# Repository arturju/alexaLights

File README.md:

# alexaLights
----
My original intent was to integrate a Particle Photon board with an Amazon Echo device to control some devices using voice commands. In the process, I found projects by people who had done similar things (see references) and used those as guides. This is my attemt at bringing together a few of the things I learned on the way.

First, the user issues a voice command to the Amazon Echo device. The device sends the audio to Amazon's Alexa Voice service which 'tokenizes' the speech into a json format. It then gets routed to the specified endpoint (our AWS Lambda Function) and passes the tokenized values into the function call to Particle's API. This triggers our Particle Photon device to change state and return an *int* to the Lambda Function. The Lambda Function finishes the request and sends a voice response back for the Amazon Echo device along with an optional reference card for the companion app.

----
## Hardware and Particle

Let's start at the last step of the process; the Particle Photon. I wanted to control an LED strip which needed a voltage higher than what the Particle Photon could provide so I got a [power supply](https://www.amazon.com/gp/product/B005T7NIAI/ref=oh_aui_detailpage_o06_s00?ie=UTF8&psc=1) that could provide 24V for the LED strip and 5V for for the board. To switch this load I used a [TIP120](https://www.adafruit.com/product/976) Darlington transistor and wired it to the board according to the schematics. Finally, a [PIR sensor](https://www.adafruit.com/product/189) allows the controller to automatically turn the lights on/off if certain timers have elapsed.

The main loop in the Photon runs a state machine that reads any inputs, updates the status of pins, checks flags and timers, and remembers the last state of the input pin. The following lines of code connect the locally defined functions, *turnPinOnOff* and *partyFunc*, to Particle's cloud. This will allow us to call these functions from other code.
```C
    Spark.function("myFunction", turnPinOnOff);
    Spark.function("globalParty", partyFunc);
```
Calling the function will trigger a change in one of the flags or pin values and this gets picked up the next time the main loops runs through.

----
## Lambda Function

I won't go into detail on how to create an AWS account (you can see the tutorials on the references for more details) but I'll touch on some points that I think are important. The relevant files for the Lambda Function are in the *customSkill/src/* directory (more about Smart Home Skills in a bit). You will need to edit the *sampleConfig.js* file with your Particle board's information, your deviceID and acccesToken, and rename it to *config.js*. 
The main code is in *index.js* file but before we take a look at it we must understand the structure of an Alexa Custom Skill command. A command consists of a **wake word**, Alexa, an **invocation name** and an **intent** with optional **slots**.

The Lambda Function receives the aforementioned parameters in a JSON format (more on this later), switches to the appropiate case based on the **intent**, uses the **slots** to construct a message, and sends it off to the Particle board. Many Intents can be assigned to the Custom Skill giving it much more versatility than a Smart Home Skill. 

We can also design a response card to the companion Alexa App that can display extra information for the user. The fastest way to get up and running is to select *AlexaSkill.js, config.js, index.js* zip them, and upload directly to the Lambda Function page.

For the user, the main difference between a Custom Skill and a Smart Home Skill is the way in which it's called. A Smart Home Skill does not need an invocation name, so our command would be _'Alexa, turn the Kitchen Lights On'_. This is much easier to remember but unfortunately the backend limits the responses back to the users and requires an OAuth to authenticate with your device making things a bit more complicated. I was not able to succesfully authenticate with my Particle device but I put the code up anyways in case anyone wants to try it. That's in the _smartHomeSkill/_ directory.

----
## Alexa Skills Kit (ASK)

This part of the code is responsible for defining your **invocation name**, **intents**, and **slots** (code can be found in *customSkill/speechAssets/*). The Interaction Model of the Custom Skill contains Sample Utterances that are used to correctly identify your request. For example, the *onOffIntent* is defined by the phrase ('Alexa, *tell/ask* *The House*' is assummed) 'to turn the _Kitchen Lights_ _Off_'. 
```
onOffIntent to turn the {deviceName} {onOrOff}
```
The Intent Schema connects your Sample Utterances to the JSON format in which it will get passed to the Lambda Function. For the onOffIntent we have the following Intent Schema:

``` javascript
{
 "intents": [
   {
    "intent": "onOffIntent",
     "slots": [
       {
        "name": "onOrOff",
        "type": "ON_OFF"
       },
       {
        "name": "deviceName",
        "type": "DEVICE_NAMES"
       }
      ] 
   }
  ]
}
```
The last important part of the Alexa Skill Kit are the Custom Slot Types which are like macros. For example:
```
DEVICE_NAMES
kitchen lights
living room lights
```

----
## Result

Picture and video:

----

## References:

##### Custom Skill:
* [alexaParticleBridge](https://github.com/rlisle/alexaParticleBridge)
* [Particle_Alexa](https://github.com/krvarma/Particle_Alexa)

##### Smart Home Skill:
* [Steps to Create a Smart Home Skill](https://developer.amazon.com/public/solutions/alexa/alexa-skills-kit/docs/steps-to-create-a-smart-home-skill)
* [particle-alexa-smart-home-skill](https://github.com/krvarma/particle-alexa-smart-home-skill) 

##### To-do:
* [Push Notifications](https://forums.developer.amazon.com/questions/40799/workaround-for-push-notifications.html)

---

You can see more of my projects at [here](http://ajumpa.com/)

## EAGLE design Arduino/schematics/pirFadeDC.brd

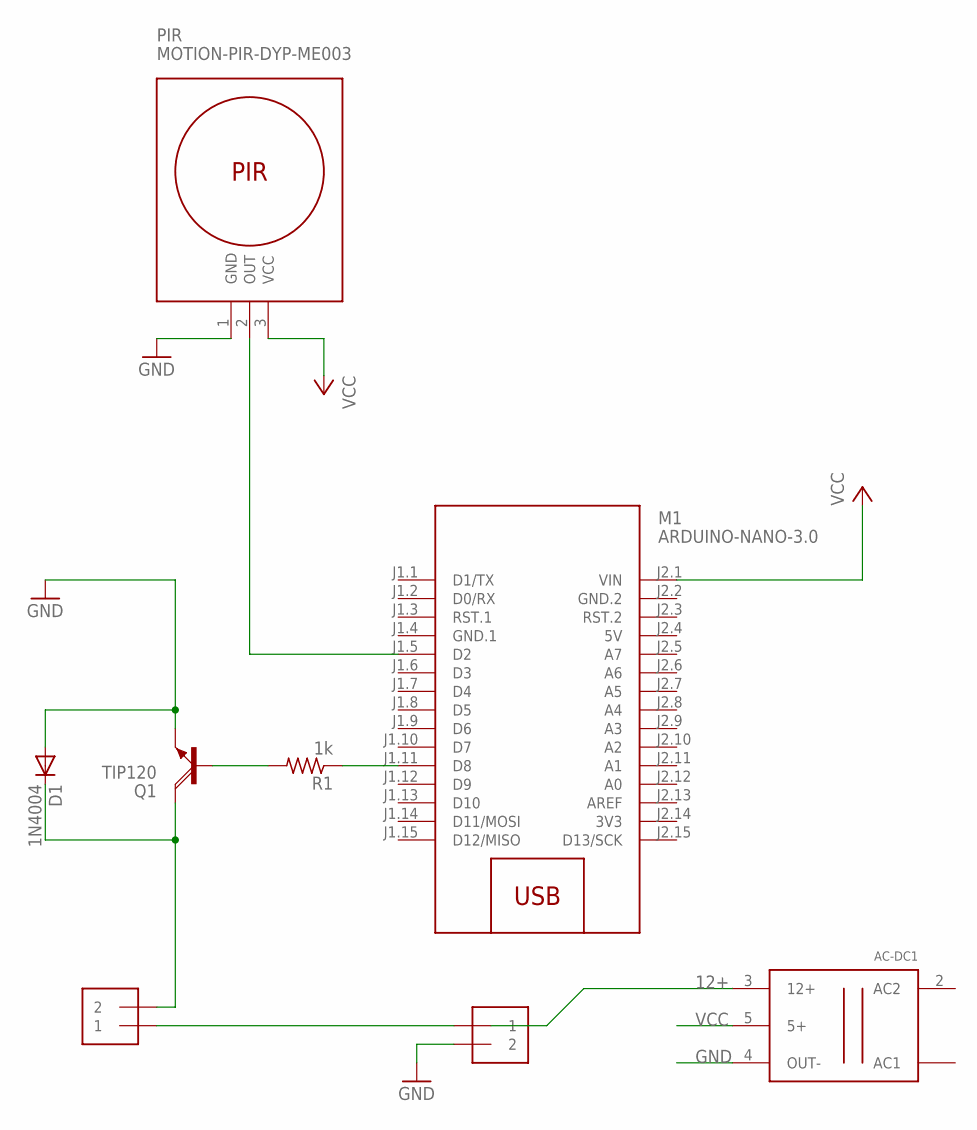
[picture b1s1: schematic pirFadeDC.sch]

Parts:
AC-DC1: GENERIC_AC/DC; AC/DC
D1: 1N4004; DO41-10
J1, J2: 1X2-3.5MM
M1: ARDUINO-NANO-3.0
PIR: MOTION-PIR-DYP-ME003
Q1: TIP120; TO220AH
R1: 1k; 0805-THM

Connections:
3V3: M1.J2.14 (3V3)
5V: M1.J2.4 (5V)
12+: AC-DC1.3 (12+)
GND: AC-DC1.4 (OUT-), D1.A, J2.2, PIR.1 (GND), Q1.E
GND.1: M1.J1.4 (GND.1)
GND.2: M1.J2.2 (GND.2)
unnamed: M1.J1.11 (D8), R1.1
unnamed: Q1.B, R1.2
unnamed: J1.1, J2.1
unnamed: M1.J1.5 (D2), PIR.2 (OUT)
unnamed: D1.C, J1.2, Q1.C
VCC: AC-DC1.5 (5+), M1.J2.1 (VIN), PIR.3 (VCC)

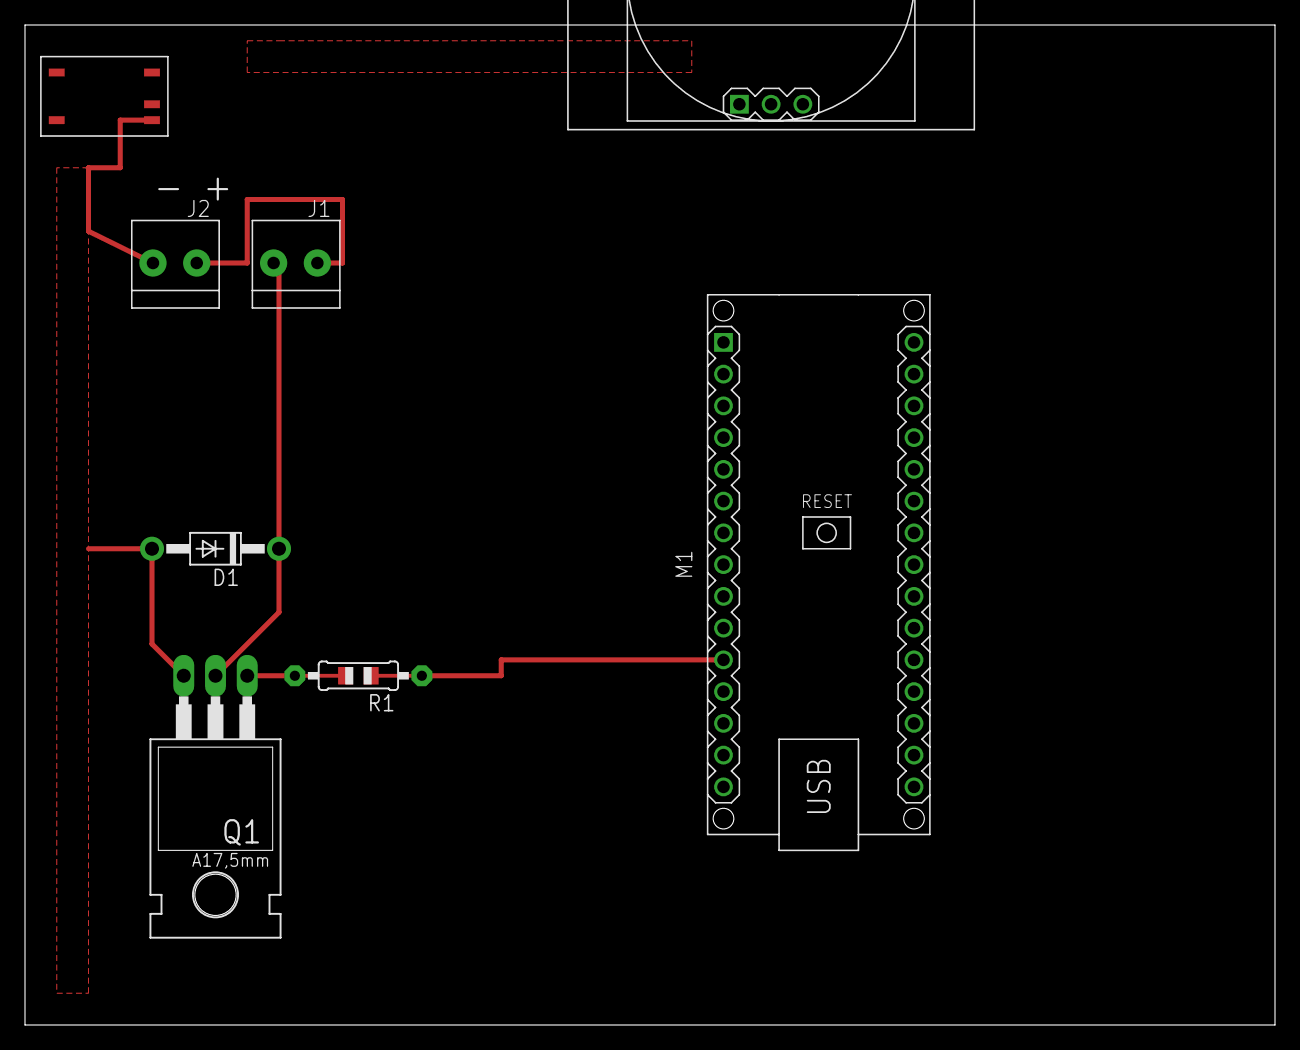
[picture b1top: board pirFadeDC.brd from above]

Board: 2 copper layers, 100.0 x 80.0 mm, 8 parts (0 on the bottom side), 7 nets.

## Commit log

2017-03-25 Initial commit after configuring .gitignore and putting personal info in config.js
2017-03-27 organized files. Wrote references for readme
2017-03-29 Added picture of diagram, fritzing and assembly
2017-03-29 Wrote more on readme. Do relative links for images work? let's test
2017-04-01 Added invocation image and wrote more readMe stuffs
2017-04-01 Wrote more for readme and linked in youtube video

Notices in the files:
parts and their libraries:
diy-modules: Released under the Creative Commons Attribution 4.0 International License: http://creativecommons.org/licenses/by/4.0
